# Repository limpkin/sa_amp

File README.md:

# sa_amp
A low noise DC to 600kHz amplifier

Main Specifications
- 0mV output offset voltage  
- 22dBm maximum output level  
- typical 0.9nV/sq(Hz) noise floor  
- 34dB gain between DC and 375kHz (.1dB)  
- 34dB gain between DC and 600kHz (3dB)  
- clipper activation artifact: 800ns 4V pulse (see here)

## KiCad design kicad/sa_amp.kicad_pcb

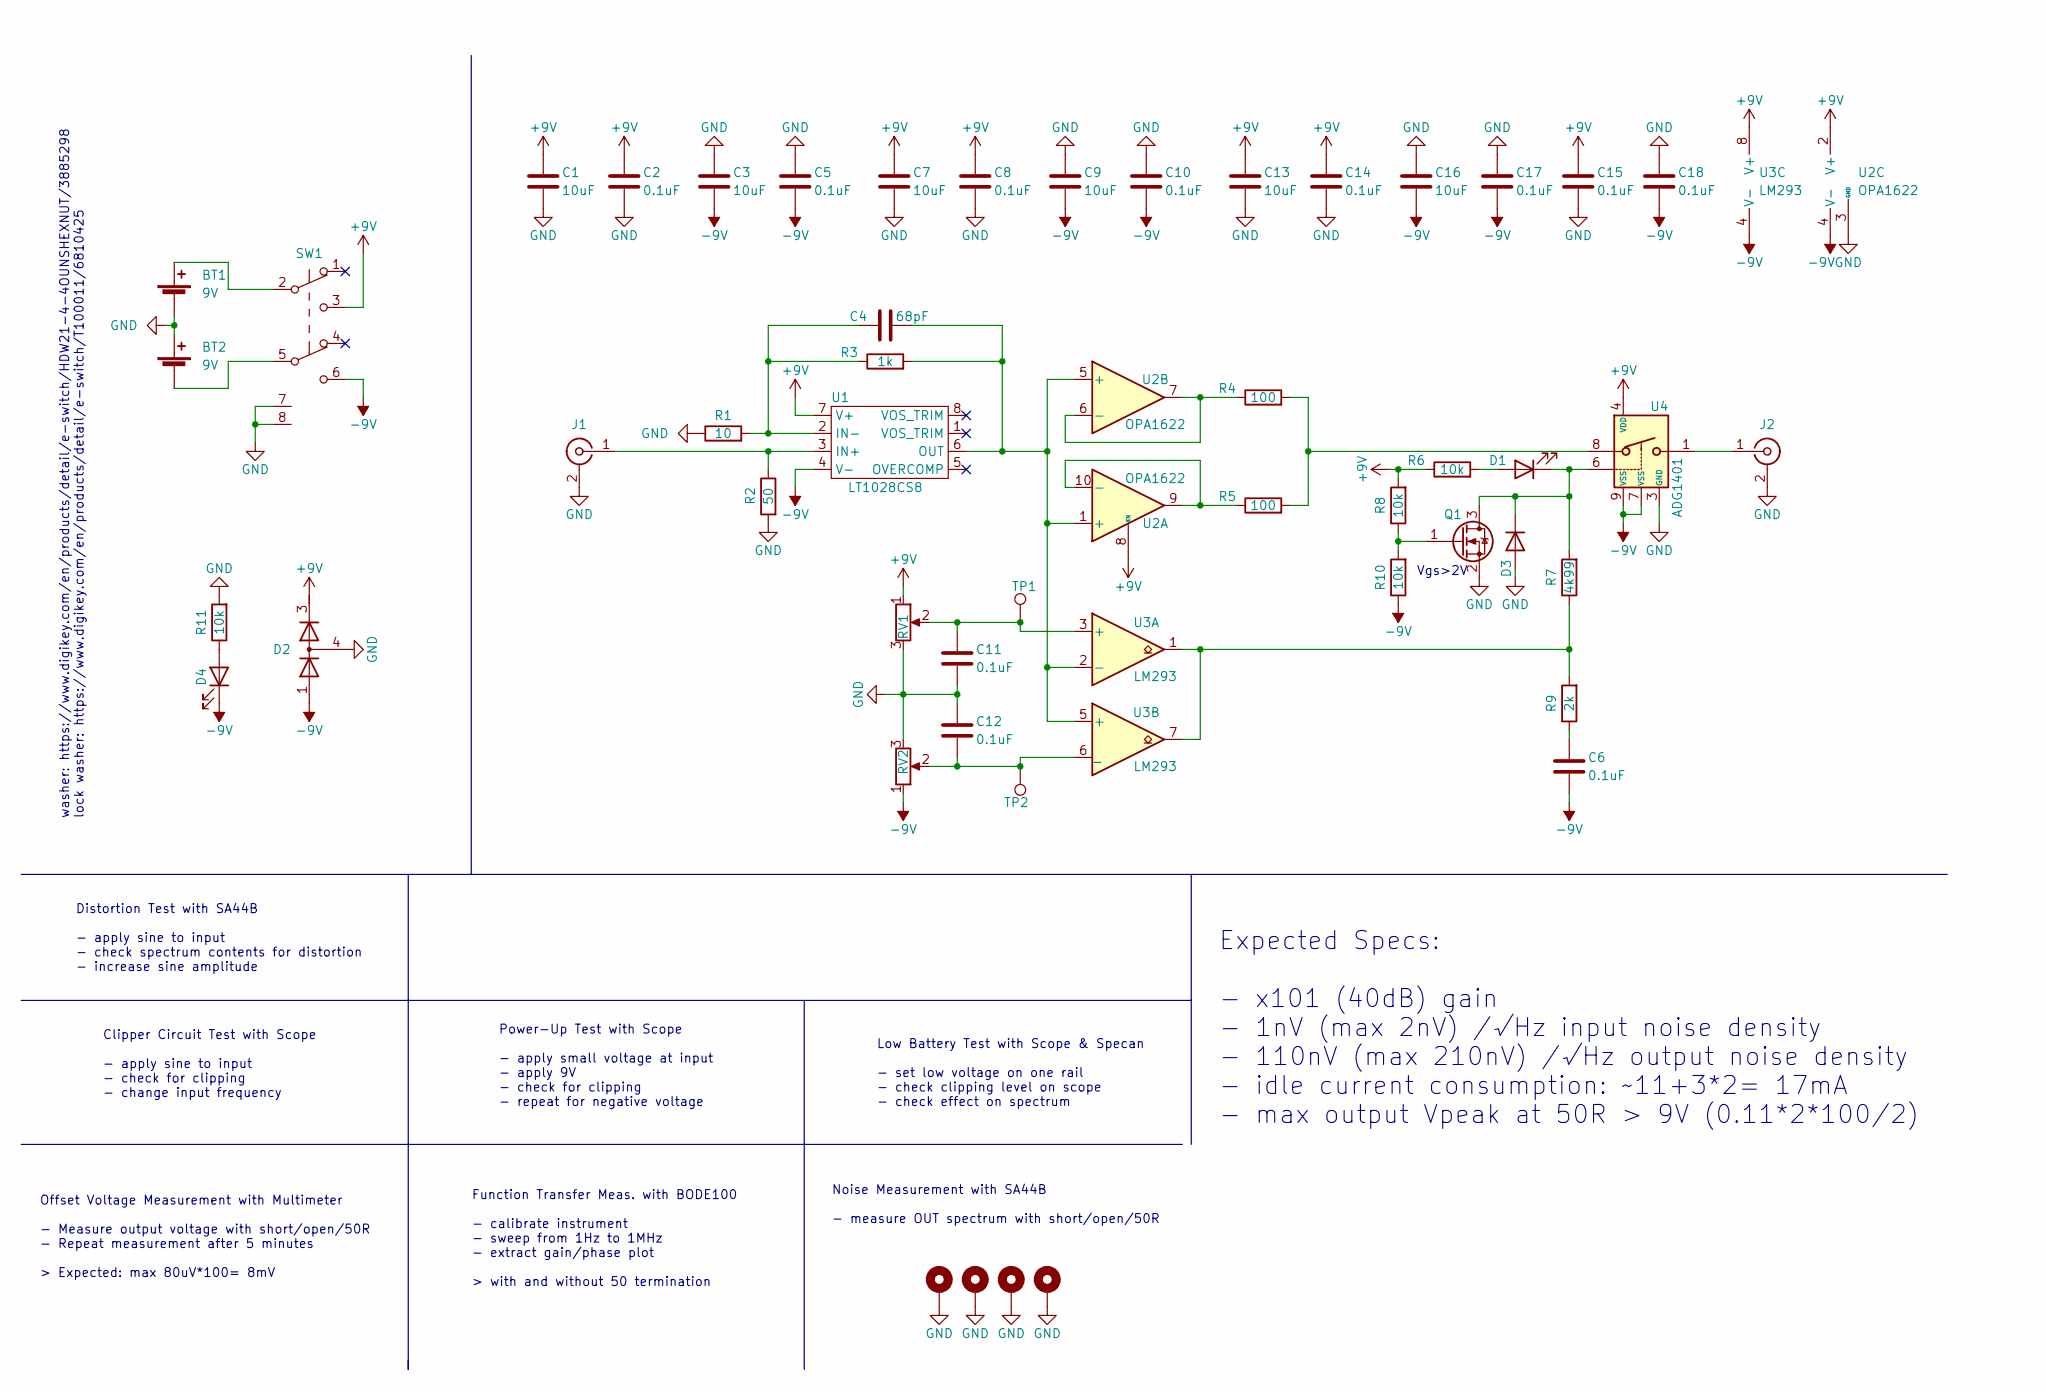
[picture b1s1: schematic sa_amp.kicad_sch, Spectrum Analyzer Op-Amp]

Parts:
BT1, BT2: 9V; PinSocket_2x01_P2.00mm_Vertical
C1, C3, C7, C9, C13, C16: 10uF; C_0805_2012Metric
C2, C5, C6, C8, C10, C11, C12, C14, C15, C17, C18: 0.1uF; C_0603_1608Metric
C4: 68pF; C_0603_1608Metric
D1, D4: LED; LED_0603_1608Metric
D2: D_Dual_Series_bat120s; SOT-223
D3: D; D_SOD-323
H1, H2, H3, H4: MountingHole_Pad; MountingHole_2.7mm_M2.5_Pad_TopOnly
J1, J2: Conn_Coaxial; 132139_LP
Q1: Q_NMOS_GSD; SOT-23
R1: 10; R_0603_1608Metric
R2: 50; R_0603_1608Metric
R3: 1k; R_0603_1608Metric
R4, R5: 100; R_0805_2012Metric
R6, R8, R10, R11: 10k; R_0603_1608Metric
R7: 4k99; R_0603_1608Metric
R9: 2k; R_0603_1608Metric
RV1, RV2: R_Potentiometer; Potentiometer_Bourns_3214W_Vertical
SW1: SW_Push_DPDT_100DP1T1B1M6QE; 100DP1T1B1M6QE
TP1, TP2: TestPoint; TestPoint_Pad_2.0x2.0mm
U1: LT1028CS8; SO-8_3.9x4.9mm_P1.27mm
U2: OPA1622; Texas_S-PVSON-N10
U3: LM293; TSSOP-8_4.4x3mm_P0.65mm
U4: ADG1401; WDFN-8-1EP_3x2mm_P0.5mm_EP1.65x1.8mm

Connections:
+9V: C1.1, C2.1, C7.1, C8.1, C13.1, C14.1, C15.1, D2.3 (K), R6.1, R8.2, RV1.1, SW1.3 (C), U1.7 (V+), U2.2 (V+), U2.8 (EN), U3.8 (V+), U4.4 (VDD)
-9V: C3.2, C5.2, C6.2, C9.2, C10.2, C16.2, C17.2, C18.2, D2.1 (A), D4.1 (K), R10.1, RV2.1, SW1.6 (C), U1.4 (V-), U2.4 (V-), U2.11 (V-), U3.4 (V-), U4.7 (VSS), U4.9 (VSS)
GND: BT1.2 (-), BT2.1 (+), C1.2, C2.2, C3.1, C5.1, C7.2, C8.2, C9.1, C10.1, C11.2, C12.1, C13.2, C14.2, C15.2, C16.1, C17.1, C18.1, D2.4 (common), D3.2 (A), H1.1, H2.1, H3.1, H4.1, J1.2 (Ext), J2.2 (Ext), Q1.2 (S), R1.1, R2.2, R11.2, RV1.3, RV2.3, SW1.7 (SHLD), SW1.8 (SHLD), U2.3 (GND), U4.3 (GND)
unnamed: BT1.1 (+), SW1.2 (B)
unnamed: BT2.2 (-), SW1.5 (B)
unnamed: C4.1, R1.2, R3.1, U1.2 (IN-)
unnamed: C4.2, R3.2, U1.6 (OUT), U2.1 (+), U2.5 (+), U3.2 (-), U3.5 (+)
unnamed: C6.1, R9.1
unnamed: C11.1, RV1.2, TP1.1, U3.3 (+)
unnamed: C12.2, RV2.2, TP2.1, U3.6 (_)
unnamed: D1.1 (K), D3.1 (K), Q1.3 (D), R7.2, U4.6
unnamed: D1.2 (A), R6.2
unnamed: D4.2 (A), R11.1
unnamed: J1.1 (In), R2.1, U1.3 (IN+)
unnamed: J2.1 (In), U4.1
unnamed: Q1.1 (G), R8.1, R10.2
unnamed: R4.1, U2.6 (-), U2.7
unnamed: R4.2, R5.2, U4.8
unnamed: R5.1, U2.9, U2.10 (-)
unnamed: R7.1, R9.2, U3.1, U3.7

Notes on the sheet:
Vgs>2V
Power-Up Test with Scope - apply small voltage at input - apply 9V - check for clipping - repeat for negative voltage
Low Battery Test with Scope & Specan - set low voltage on one rail - check clipping level on scope - check effect on spectrum
Clipper Circuit Test with Scope - apply sine to input - check for clipping - change input frequency
washer: https://www.digikey.com/en/products/detail/e-switch/HDW21-4-4OUNSHEXNUT/3885298 lock washer: https://www.digikey.com/en/products/detail/e-switch/T100011/6810425
Distortion Test with SA44B - apply sine to input - check spectrum contents for distortion - increase sine amplitude
Noise Measurement with SA44B - measure OUT spectrum with short/open/50R
Offset Voltage Measurement with Multimeter - Measure output voltage with short/open/50R - Repeat measurement after 5 minutes > Expected: max 80uV*100= 8mV
Expected Specs: - x101 (40dB) gain - 1nV (max 2nV) /√Hz input noise density - 110nV (max 210nV) /√Hz output noise density - idle current consumption: ~11+3*2= 17mA - max output Vpeak at 50R > 9V (0.11*2*100/2)
Function Transfer Meas. with BODE100 - calibrate instrument - sweep from 1Hz to 1MHz - extract gain/phase plot > with and without 50 termination

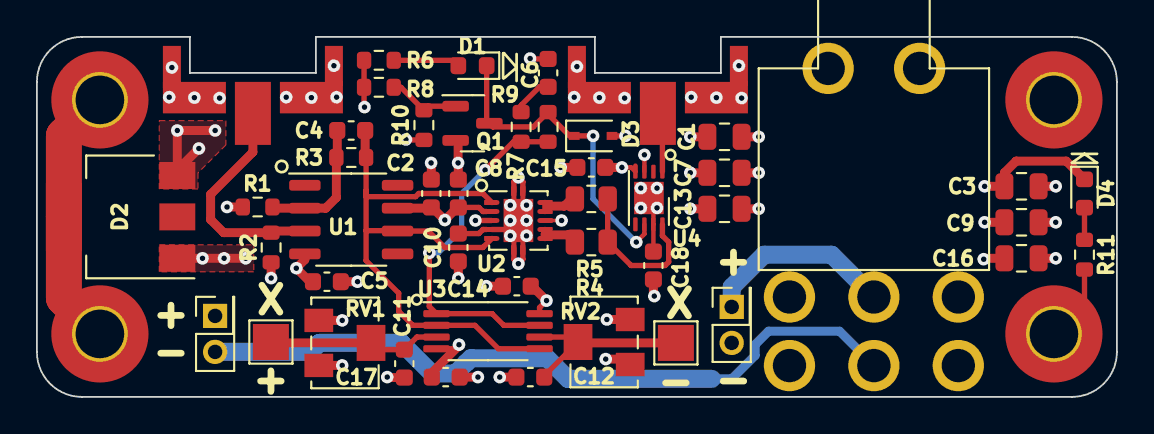
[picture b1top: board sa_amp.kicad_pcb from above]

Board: 4 copper layers, 60.0 x 20.0 mm, 51 parts (0 on the bottom side), 20 nets.

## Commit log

2023-04-01 pictures
2023-04-01 spectrum upload

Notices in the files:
kicad/sa_amp.kicad_pcb:
CERN OHL
